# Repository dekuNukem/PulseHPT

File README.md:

# PulseHPT 3-in-1 Shutter Speed Tester

[Purchase](https://www.tindie.com/products/33002/) | [Discord](https://discord.gg/yyRq8QtX4r) | [Instructions](#user-manual)

---

PulseHPT is a compact shutter speed tester for vintage cameras.

Quick and easy measurement from **multiple sources**:

* **Hot Shoe**
* **PC Socket**
* **Light Sensor**
	* Built-in & External
	* Leaf Shutter: All Speeds
	* Focal Plane Shutter: Within Flash Sync

Ideal for **in-the-field testing** of unknown cameras

## Highlights

* Compact & Portable

* Multiple Sources

* Microsecond Accuracy

* 20-hour battery / 4000 measurements

## Buy One / Discussions

* United Kingdom: [https://www.ebay.co.uk/itm/365904291256](https://www.ebay.co.uk/itm/365904291256)

* Rest of the world: [https://www.tindie.com/products/33002/](https://www.tindie.com/products/33002/)

[Discord chatroom](https://discord.gg/yyRq8QtX4r) for questions and discussions. Or email `dekuNukem`@`gmail`.`com` .
 
# User Manual

- [Battery](#battery)

- [Hot Shoe](#measurement-hot-shoe)

- [PC Socket](#measurement-pc-socket)

- [Built-in Light Sensor](#measurement-light-sensor)

- [External Light Sensor](#external-light-sensor)

## Battery

* **CR2032**

* Positive (+) side up

* ⚠️ Slide UNDER the catch!

## Measurement: Hot Shoe

* Insert into hot shoe
* Slide switch to ON
* Select a speed
	* Leaf Shutter: All Speeds
	* Focal Plane Shutter: **Within Flash Sync Speed**
* Wind and release the shutter

💭 If nothing happens, press down to ensure good contact.

⚠️ **Beware of caveats!** Read below.

#### How it works

When taking a photo, the flash sync signal activates, and remains active **until shutter is closed**.

Thus the approximate shutter speed can be measured.

#### Caveats

* Flash sync fires **only when shutter is fully open**.

* Thus at higher speeds, the measured speed can be faster than real speed.

* Works best with earlier mostly-mechanical cameras.

* For most accurate result, use the light sensor method.

## Measurement: PC Socket

* Use a common **PC socket to 3.5mm Jack** Cable

* Plug into PC socket, and the other end in the tester.

* ⚠️ ⚠️ Make sure to use `X Sync` socket / option!

* Slide switch to ON
* Select a speed
	* Leaf Shutter: All Speeds
	* Focal Plane Shutter: **Within Flash Sync Speed**
* Wind and release the shutter

💭 If nothing happens, apply **GENTLE** pressure on the PC socket to ensure good contact.

⚠️ Same caveats as hot shoe!

## Measurement: Light Sensor

* Most accurate
* Two Sources
	* Built-in Sensor: Easiest to Use
	* External Sensor: More Consistent Setup

## Built-in Light Sensor

The built-in sensor sticks out on the left-hand side.

Slide the light sensor source switch to `INTERAL` position.

Shine a bright light into the sensor.

It should trigger and give a measurement.

Now you know how bright the light needs to be.

To test:

* Remove lens if possible
	* Largest aperture otherwise
* Shine light from front
* Place tester **near the center** of film gate
* Fire shutter
	* Leaf Shutter: All Speeds
	* Focal Plane Shutter: **Within Flash Sync Speed**

## External Light Sensor

Requires more setup, but can be more consistent. Also suitable for hard-to-reach places.

* Locate the connector on **bottom-left corner**.

* **SLOWLY and GENTLY** push the black tab outwards to unlock.

* Insert the ribbon cable **metal contact side up** all the way in

* Push the tab back in to lock

* **Do the same** on the sensor side

* Slide Source Switch to `EXTERNAL`

With light sensor connected, let's do a quick test!

* Briefly shine a bright light on the sensor

* Result will be shown

* Now you know how bright the light needs to be

Use double side tape, mount the sensor on a vertical surface, e.g. a box.

* Test **without lens** if possible
	* Largest aperture otherwise
* Sensor behind shutter
* Shine light
* If possible, use Bulb mode to ensure sensor is at the **center of the light circle**.

* Fire shutter
	* Leaf Shutter: All Speeds
	* Focal Plane Shutter: **Within Flash Sync Speed**

## Questions or Comments?

[Discord chatroom](https://discord.gg/yyRq8QtX4r) for questions and discussions. Or email `dekuNukem`@`gmail`.`com` .

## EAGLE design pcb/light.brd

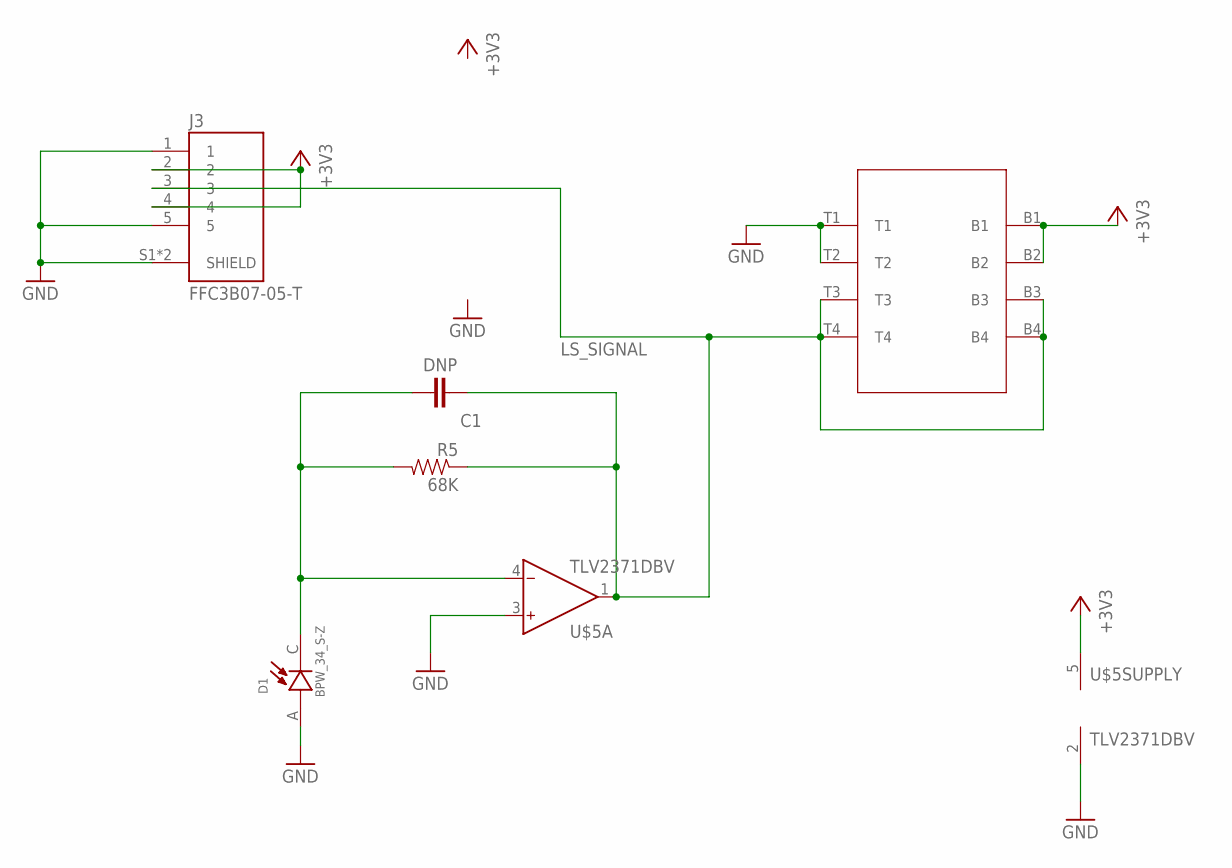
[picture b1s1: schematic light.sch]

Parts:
C1: DNP; 0805
D1: BPW_34_S-Z; DIO_BPW_34_S-Z
J3: FFC3B07-05-T; GCT_FFC3B07-05-T
R5: 68K; 0805
U$1: LS_VERT
U$5: TLV2371DBV; SOT23-5L

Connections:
+3V3: J3.2, J3.4, U$1.B1, U$1.B2, U$5.5 (V+)
GND: D1.A, J3.1, J3.5, J3.S1 (SHIELD), J3.S2 (SHIELD), U$1.T1, U$1.T2, U$5.2 (V-), U$5.3 (IN+)
LS_SIGNAL: C1.1, J3.3, R5.1, U$1.B3, U$1.B4, U$1.T3, U$1.T4, U$5.1 (OUT)
unnamed: C1.2, D1.C, R5.2, U$5.4 (IN-)

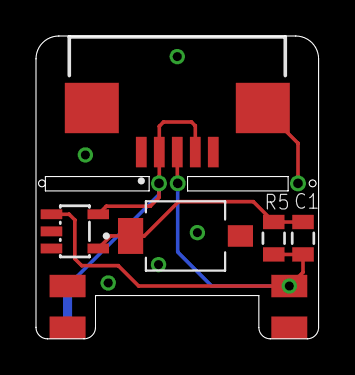
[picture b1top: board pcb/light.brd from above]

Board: 2 copper layers, 15.7 x 16.8 mm, 6 parts (0 on the bottom side), 4 nets.

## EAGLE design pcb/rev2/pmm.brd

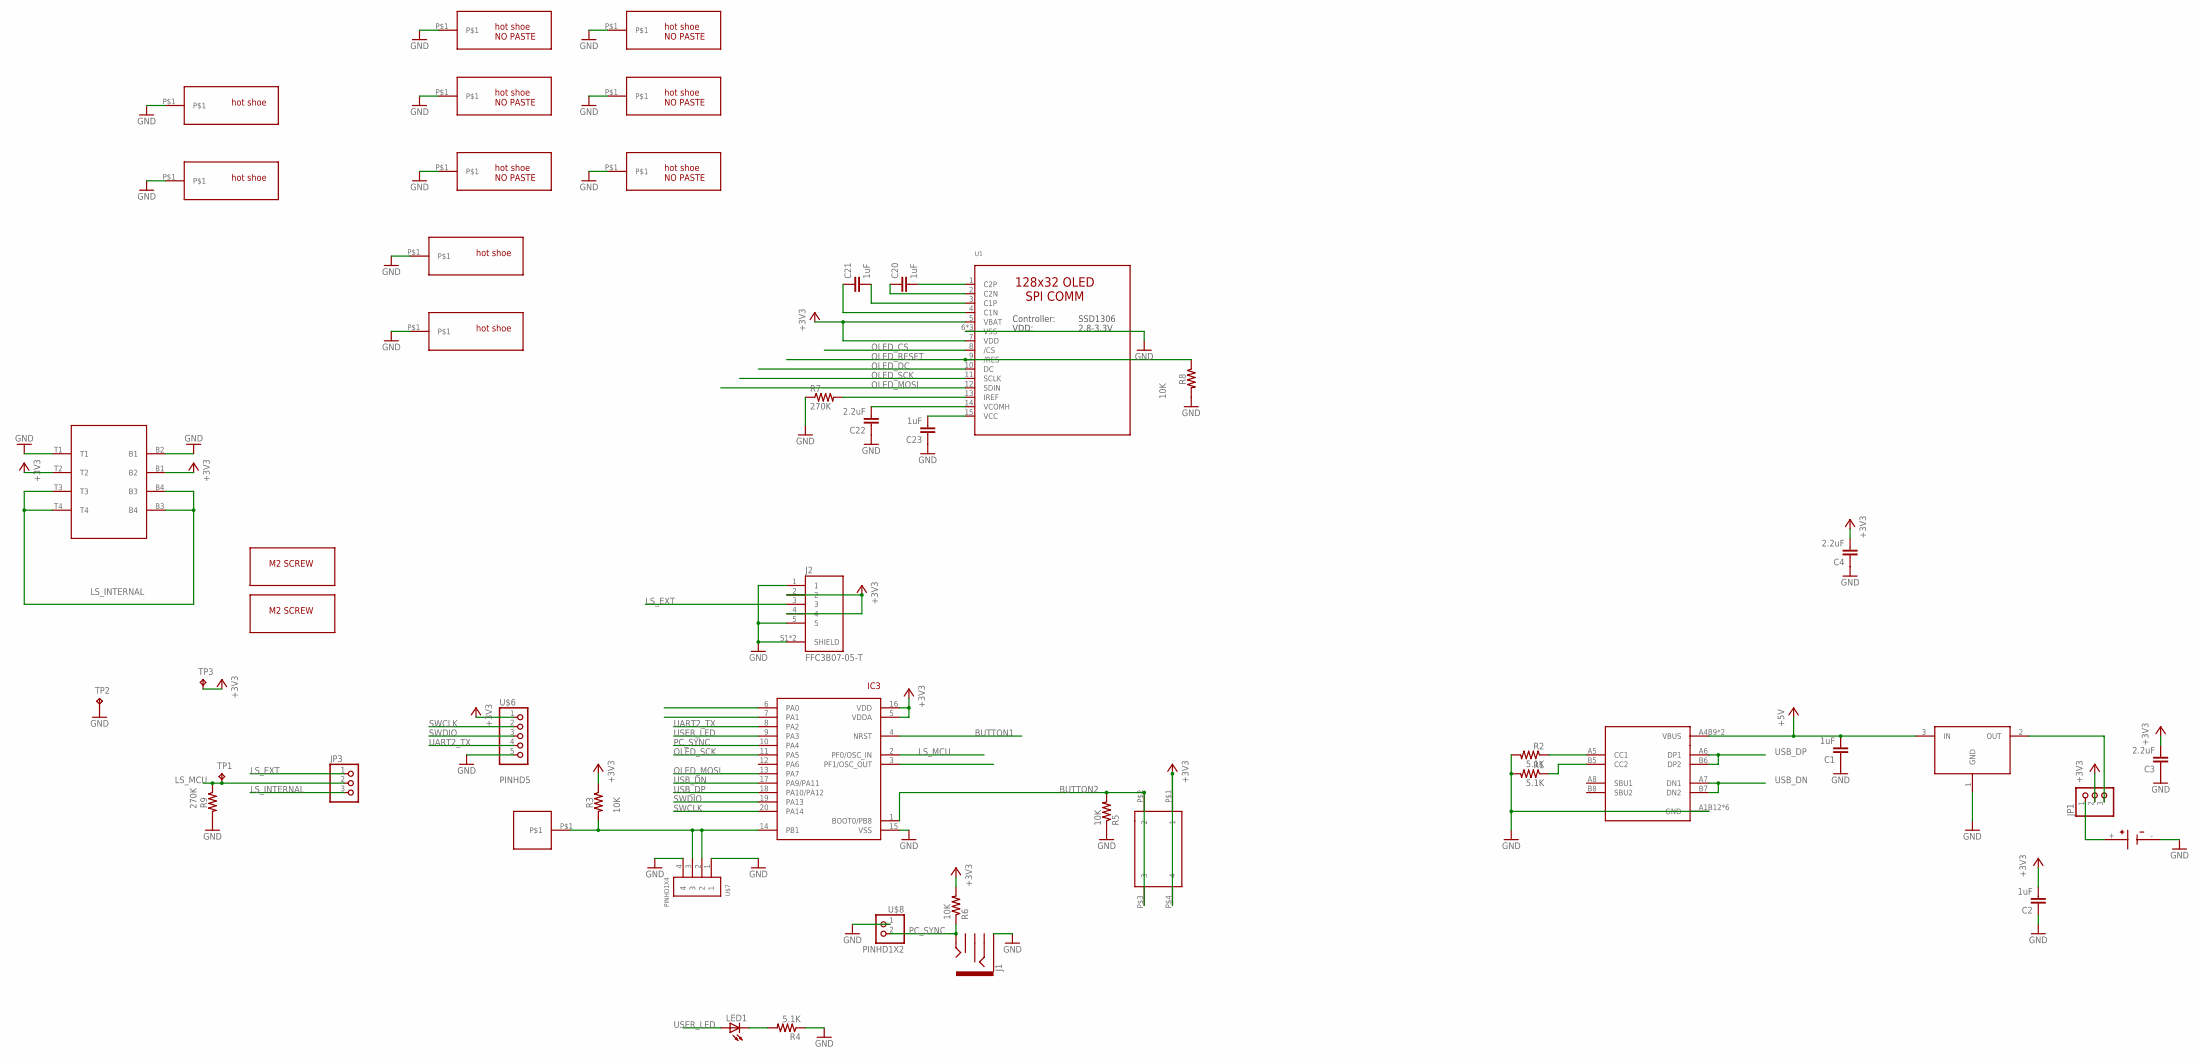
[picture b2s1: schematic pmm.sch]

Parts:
BT1: BU2032SM-G; BAT_BU2032SM-G
C1, C2, C20, C21, C23: 1uF; 0805
C3, C4, C22: 2.2uF; 0805
IC3: STM32F042F4; TSSOP20
J1: AUDIO_JACK_3.5MM_PTH; AUDIO-JACK
J2: FFC3B07-05-T; GCT_FFC3B07-05-T
JP1, JP3: PINHD-1X3CB; 1X03-CLEANBIG
LED1: LEDCHIP-LED0805; CHIP-LED0805
R1, R2, R4: 5.1K; 0805
R3, R5, R6, R8: 10K; 0805
R7, R9: 270K; 0805
SW4: 324_SW; 342_SWICH_FOOT
TP1, TP2, TP3: TPTP18R; TP18R
U1: LUL_DISP_OLED_UG-2864HSWEG01; LUL_UG-2864HSWEG01_1.3_WRAPAROUND
U2: USBC_16P; USBC_16P_FOOT
U4: XC6206_DEV; SOT23R_INFINEON
U$1, U$12: M2_SCREW_DEV; M2_SCREW_FOOT
U$2: SPRING_CONTACT
U$3, U$4, U$14, U$16: HOTSHOE; HOTSHOE_RAIL
U$5, U$9, U$10, U$11, U$13, U$15: HOTSHOE_NOPASTE; HOTSHOE_RAIL_NOPASTE
U$6: PINHD5; 1X05
U$7: PINHD1X4; 1X04-CLEANBIG
U$8: PINHD1X2; 1X02
U$17: LS_HOLE; LS

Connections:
+3V3: C2.2, C3.2, C4.2, IC3.5 (VDDA), IC3.16 (VDD), J2.2, J2.4, JP1.2, R3.1, R6.2, SW4.P$1 (1), SW4.P$4 (4), TP3.TP, U1.5 (VBAT), U1.7 (VDD), U$6.1, U$17.B1 (B2), U$17.T2
+5V: C1.2, U2.A4B9 (VBUS), U2.B4A9 (VBUS), U4.3 (IN)
BUTTON2: IC3.1 (BOOT0/PB8), R5.2, SW4.P$2 (2), SW4.P$3 (3)
GND: BT1.-, C1.1, C2.1, C3.1, C4.1, C22.1, C23.1, IC3.15 (VSS), J1.SLEEVE, J2.1, J2.5, J2.S1 (SHIELD), J2.S2 (SHIELD), R1.2, R2.2, R4.1, R5.1, R7.1, R8.2, R9.2, TP2.TP, U1.6 (VSS), U1.16 (VSS), U1.17 (VSS), U2.A1B12 (GND), U2.B11A12 (GND), U2.P$13 (GND), U2.P$14 (GND), U2.P$15 (GND), U2.P$16 (GND), U4.1 (GND), U$3.P$1, U$4.P$1, U$5.P$1, U$6.5, U$7.1, U$7.4, U$8.1, U$9.P$1, U$10.P$1, U$11.P$1, U$13.P$1, U$14.P$1, U$15.P$1, U$16.P$1, U$17.B2 (B1), U$17.T1; also elsewhere on the board
LS_EXT: J2.3, JP3.1
LS_INTERNAL: JP3.3, U$17.B3 (B4), U$17.B4 (B3), U$17.T3, U$17.T4
LS_MCU: IC3.2 (PF0/OSC_IN), JP3.2, R9.1, TP1.TP
unnamed: IC3.14 (PB1), R3.2, U$2.P$1, U$7.2, U$7.3
unnamed: JP1.3, U4.2 (OUT)
unnamed: LED1.C, R4.2
unnamed: R1.1, U2.B5 (CC2)
unnamed: R2.1, U2.A5 (CC1)
unnamed: C20.2, U1.1 (C2P)
unnamed: C20.1, U1.2 (C2N)
unnamed: C21.2, U1.3 (C1P)
unnamed: C21.1, U1.4 (C1N)
unnamed: R7.2, U1.13 (IREF)
unnamed: C22.2, U1.14 (VCOMH)
unnamed: C23.2, U1.15 (VCC)
OLED_CS: IC3.3 (PF1/OSC_OUT), U1.8 (/CS)
OLED_DC: IC3.7 (PA1), U1.10 (DC)
OLED_MOSI: IC3.13 (PA7), U1.12 (SDIN)
OLED_RESET: IC3.6 (PA0), R8.1, U1.9 (/RES)
OLED_SCK: IC3.11 (PA5), U1.11 (SCLK)
PC_SYNC: IC3.10 (PA4), J1.TIP, R6.1, U$8.2
RESET: IC3.4 (NRST); also elsewhere on the board
SWCLK: IC3.20 (PA14), U$6.2
SWDIO: IC3.19 (PA13), U$6.3
UART2_TX: IC3.8 (PA2), U$6.4
USB_DN: IC3.17 (PA9/PA11), U2.A7 (DN1), U2.B7 (DN2)
USB_DP: IC3.18 (PA10/PA12), U2.A6 (DP1), U2.B6 (DP2)
USER_LED: IC3.9 (PA3), LED1.A
VBAT: BT1.+, JP1.1

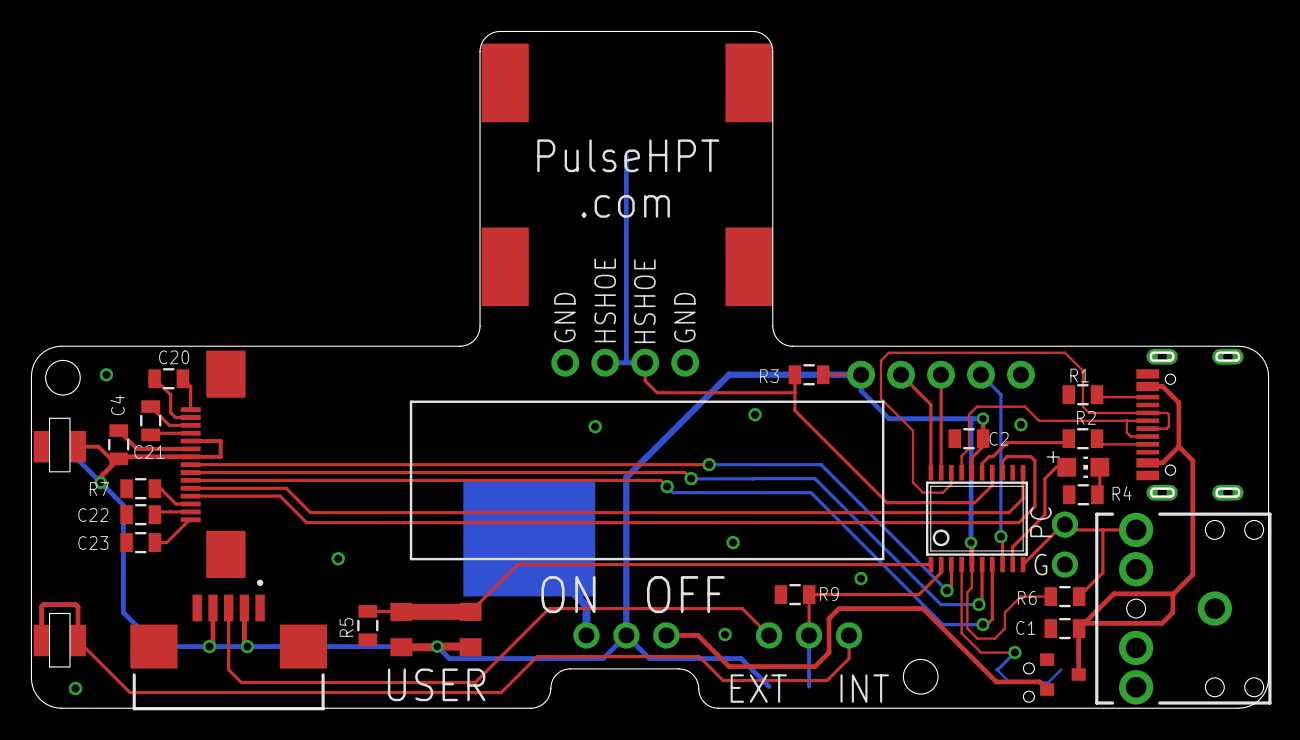
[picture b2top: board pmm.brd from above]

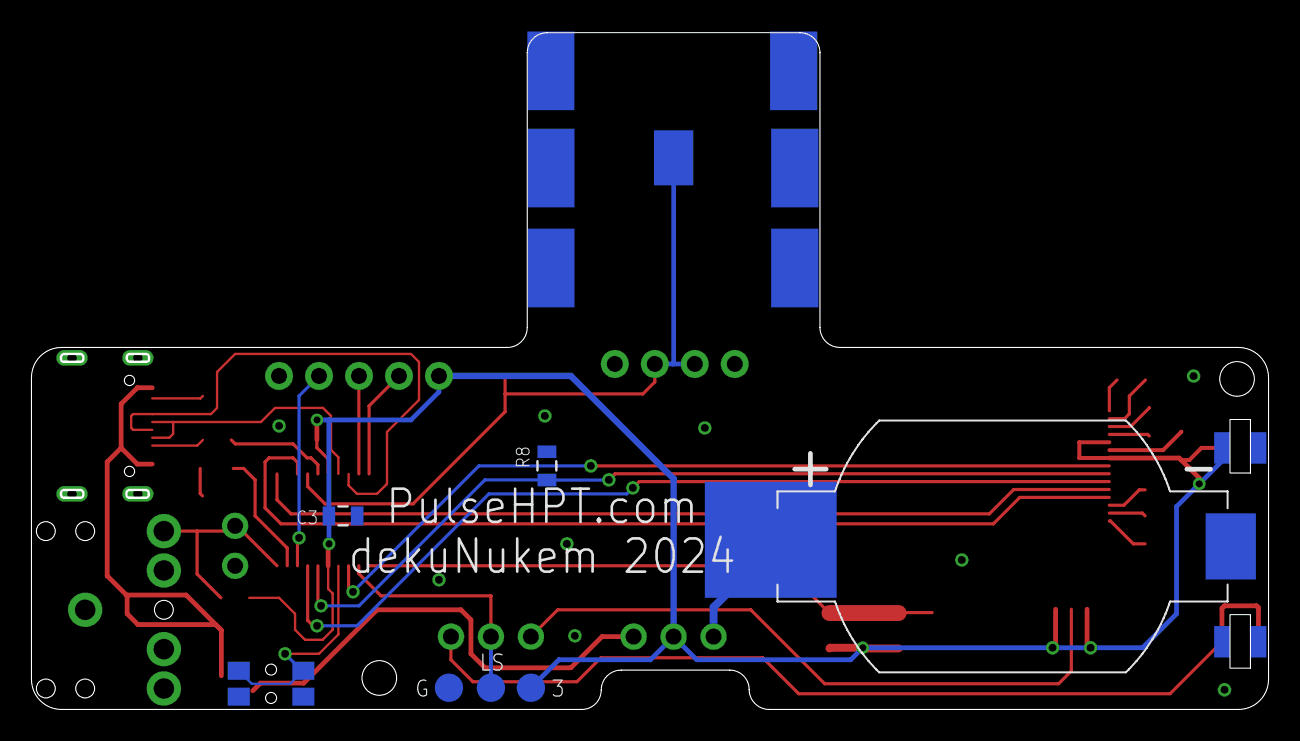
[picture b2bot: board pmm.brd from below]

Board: 2 copper layers, 78.4 x 42.8 mm, 49 parts (14 on the bottom side), 33 nets.

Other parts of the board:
SW3: 324_SW324_SWITCH_FOOT_HOLE; 342_SWICH_FOOT_HOLE

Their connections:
GND: SW3.P$2, SW3.P$3; also elsewhere on the board
RESET: SW3.P$1, SW3.P$4; also elsewhere on the board

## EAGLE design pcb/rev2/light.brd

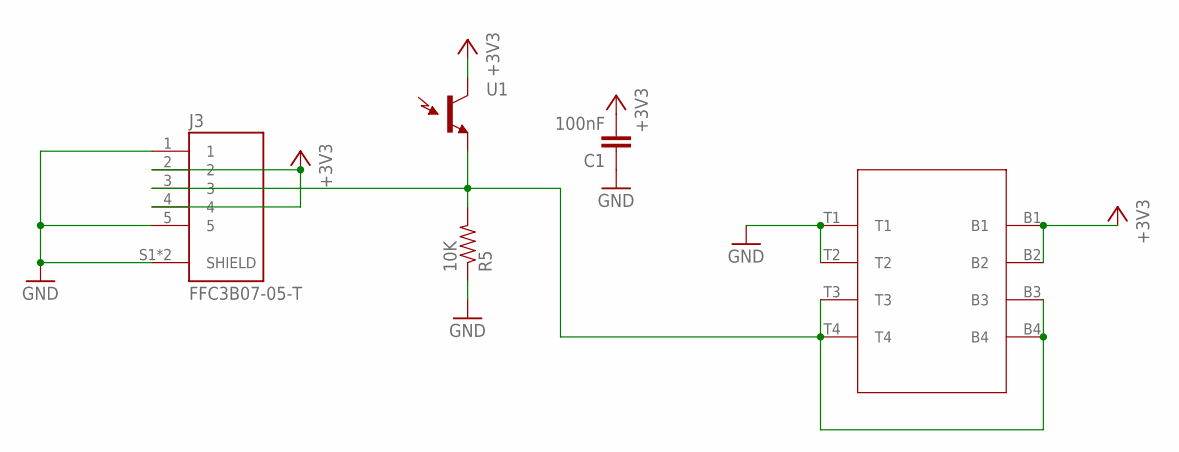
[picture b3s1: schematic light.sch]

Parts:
C1: 100nF; 0805
J3: FFC3B07-05-T; GCT_FFC3B07-05-T
R5: 10K; 0805
U1: TEMT6000; TEMT6000-SEN
U$1: LS_VERT

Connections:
+3V3: C1.2, J3.2, J3.4, U1.COLLECTOR (C1), U$1.B1, U$1.B2
GND: C1.1, J3.1, J3.5, J3.S1 (SHIELD), J3.S2 (SHIELD), R5.1, U$1.T1, U$1.T2
S: J3.3, R5.2, U1.EMITTER (E1), U$1.B3, U$1.B4, U$1.T3, U$1.T4

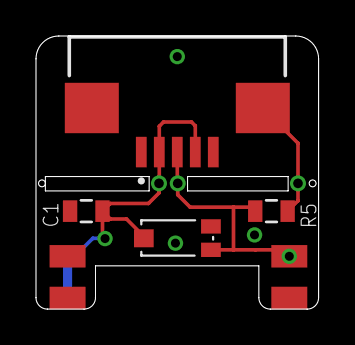
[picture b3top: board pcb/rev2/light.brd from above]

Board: 2 copper layers, 15.7 x 15.2 mm, 5 parts (0 on the bottom side), 3 nets.

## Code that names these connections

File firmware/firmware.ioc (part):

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Mcu.Name=STM32F042F6Px
Mcu.Package=TSSOP20
Mcu.UserName=STM32F042F6Px
PA0.GPIOParameters=PinState,GPIO_Label
PA0.GPIO_Label=OLED_RESET
PA0.PinState=GPIO_PIN_SET
PA0.Signal=GPIO_Output
PA1.GPIOParameters=PinState,GPIO_Label
PA1.GPIO_Label=OLED_DC
PA1.PinState=GPIO_PIN_SET
PA1.Signal=GPIO_Output
PA13.Mode=Serial_Wire
PA13.Signal=SYS_SWDIO
PA14.Mode=Serial_Wire
PA14.Signal=SYS_SWCLK
PA2.Mode=Half_duplex(single_wire_mode)
PA2.Signal=USART2_TX
PA3.GPIOParameters=GPIO_Label
PA3.GPIO_Label=USER_LED
PA3.Signal=GPIO_Output
PA4.GPIOParameters=GPIO_Label,GPIO_ModeDefaultEXTI
PA4.GPIO_Label=PC_SYNC
PA4.GPIO_ModeDefaultEXTI=GPIO_MODE_IT_RISING_FALLING
PA4.Signal=GPXTI4
PA5.Mode=Full_Duplex_Master
PA5.Signal=SPI1_SCK
PA6.Mode=Full_Duplex_Master
PA6.Signal=SPI1_MISO
PA7.Mode=Full_Duplex_Master
PA7.Signal=SPI1_MOSI
PB1.GPIOParameters=GPIO_Label,GPIO_ModeDefaultEXTI
PB1.GPIO_Label=HOTSHOE
PB1.GPIO_ModeDefaultEXTI=GPIO_MODE_IT_RISING_FALLING
PB1.Signal=GPXTI1
PB8.GPIOParameters=GPIO_Label
PB8.GPIO_Label=USER_BUTTON
PB8.Signal=GPIO_Input
PF0-OSC_IN.GPIOParameters=GPIO_PuPd,GPIO_Label,GPIO_ModeDefaultEXTI
PF0-OSC_IN.GPIO_Label=LIGHT_SENSOR
PF0-OSC_IN.GPIO_ModeDefaultEXTI=GPIO_MODE_IT_RISING_FALLING
PF0-OSC_IN.GPIO_PuPd=GPIO_PULLDOWN
PF0-OSC_IN.Signal=GPXTI0
PF1-OSC_OUT.GPIOParameters=PinState,GPIO_Label
PF1-OSC_OUT.GPIO_Label=OLED_CS
PF1-OSC_OUT.PinState=GPIO_PIN_SET
PF1-OSC_OUT.Signal=GPIO_Output
RCC.SYSCLKFreq_VALUE=8000000
board=custom

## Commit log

2023-09-23 working on pcb
2023-09-23 hotshoe done
2023-09-24 light sensor PCB
2023-09-24 shortened left side
2023-09-24 added website
2023-09-24 finishing touches
2023-09-24 added capture
2023-10-05 hello world blink working
2023-10-05 stuck at debug
2023-10-05 retarget bullshit working
2023-10-05 OLED works, removed testing
2023-10-06 exti oneedge
2023-10-06 microsecond timer and exti both edge working
2023-10-06 interrupt source working
2023-10-06 reading pin state
2023-10-06 before state machine debouncing
2023-10-07 state machine roughly working
2023-10-07 state machine working
2023-10-07 hotshoe formatting
2023-10-07 fixed glitches
2023-10-07 added notes
2023-10-07 fast LED toggle
2023-10-07 centered print, result horizotal
2023-10-08 updated result formatting, added result delay
2023-10-08 PC socket result print
2023-10-08 before multi source detect
2023-10-08 working on result consolidation
2023-10-08 before switching to sss array
2023-10-09 double triple print working
2023-10-09 added gnd via on light sensor board, fixed silkscreen
2023-10-09 fixed light sensor polarity
2023-10-09 added pulldown on light sensor pin, pcb cleanup
2023-10-09 added spring contacts
2023-10-09 pcb cleanup
2023-10-10 changed to 8MHz working
2023-10-10 oled dim working
2023-10-10 added version number display, fixed bugs
2023-10-13 adjusted resistor values
2023-10-16 updated PCB
2023-10-20 adjusted PCB
2023-10-24 cleaning up pcb
2023-11-12 writing doc
2023-11-12 switched the result display around
2023-11-13 added sources svg
2023-11-27 no dim, result blink, minor updates
2023-11-30 working on doc
2023-11-30 skipped blanking out for first measurement
2023-12-01 added light sensor instruction
2023-12-02 updated photos
2023-12-02 updated links
2023-12-04 updated discord link
2024-02-02 working on improvments
2024-02-27 adjusted for pcb thickness
2024-03-13 added more info about shutter types
2024-07-01 reset button
2024-07-16 update wording
2024-07-23 adjusted traces
2024-09-16 added dfu
2024-10-20 updated instructions for new revision with built-in sensor
2024-10-20 updated photo
2024-10-20 fixed a typo oops
2024-10-27 wtf is a jekyll
2024-10-27 trying a different theme
2024-10-28 adjusted wording
2025-01-08 kramdown test
2025-01-08 does this work
2025-01-08 nope
2025-01-08 test html image
2025-01-08 revert
2025-07-04 cleanup PCB files
2025-07-07 photodiode
2025-07-07 adjusted resistor
2025-07-16 adjusted gain resistor values, added more captures
2025-07-20 adjusted light sensor compensation
2025-09-19 try out unami
2025-11-19 updated ebay link

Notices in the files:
parts and their libraries:
SparkFun-Passives: Licensing: Creative Commons ShareAlike 4.0 International - https://creativecommons.org/licenses/by-sa/4.0
